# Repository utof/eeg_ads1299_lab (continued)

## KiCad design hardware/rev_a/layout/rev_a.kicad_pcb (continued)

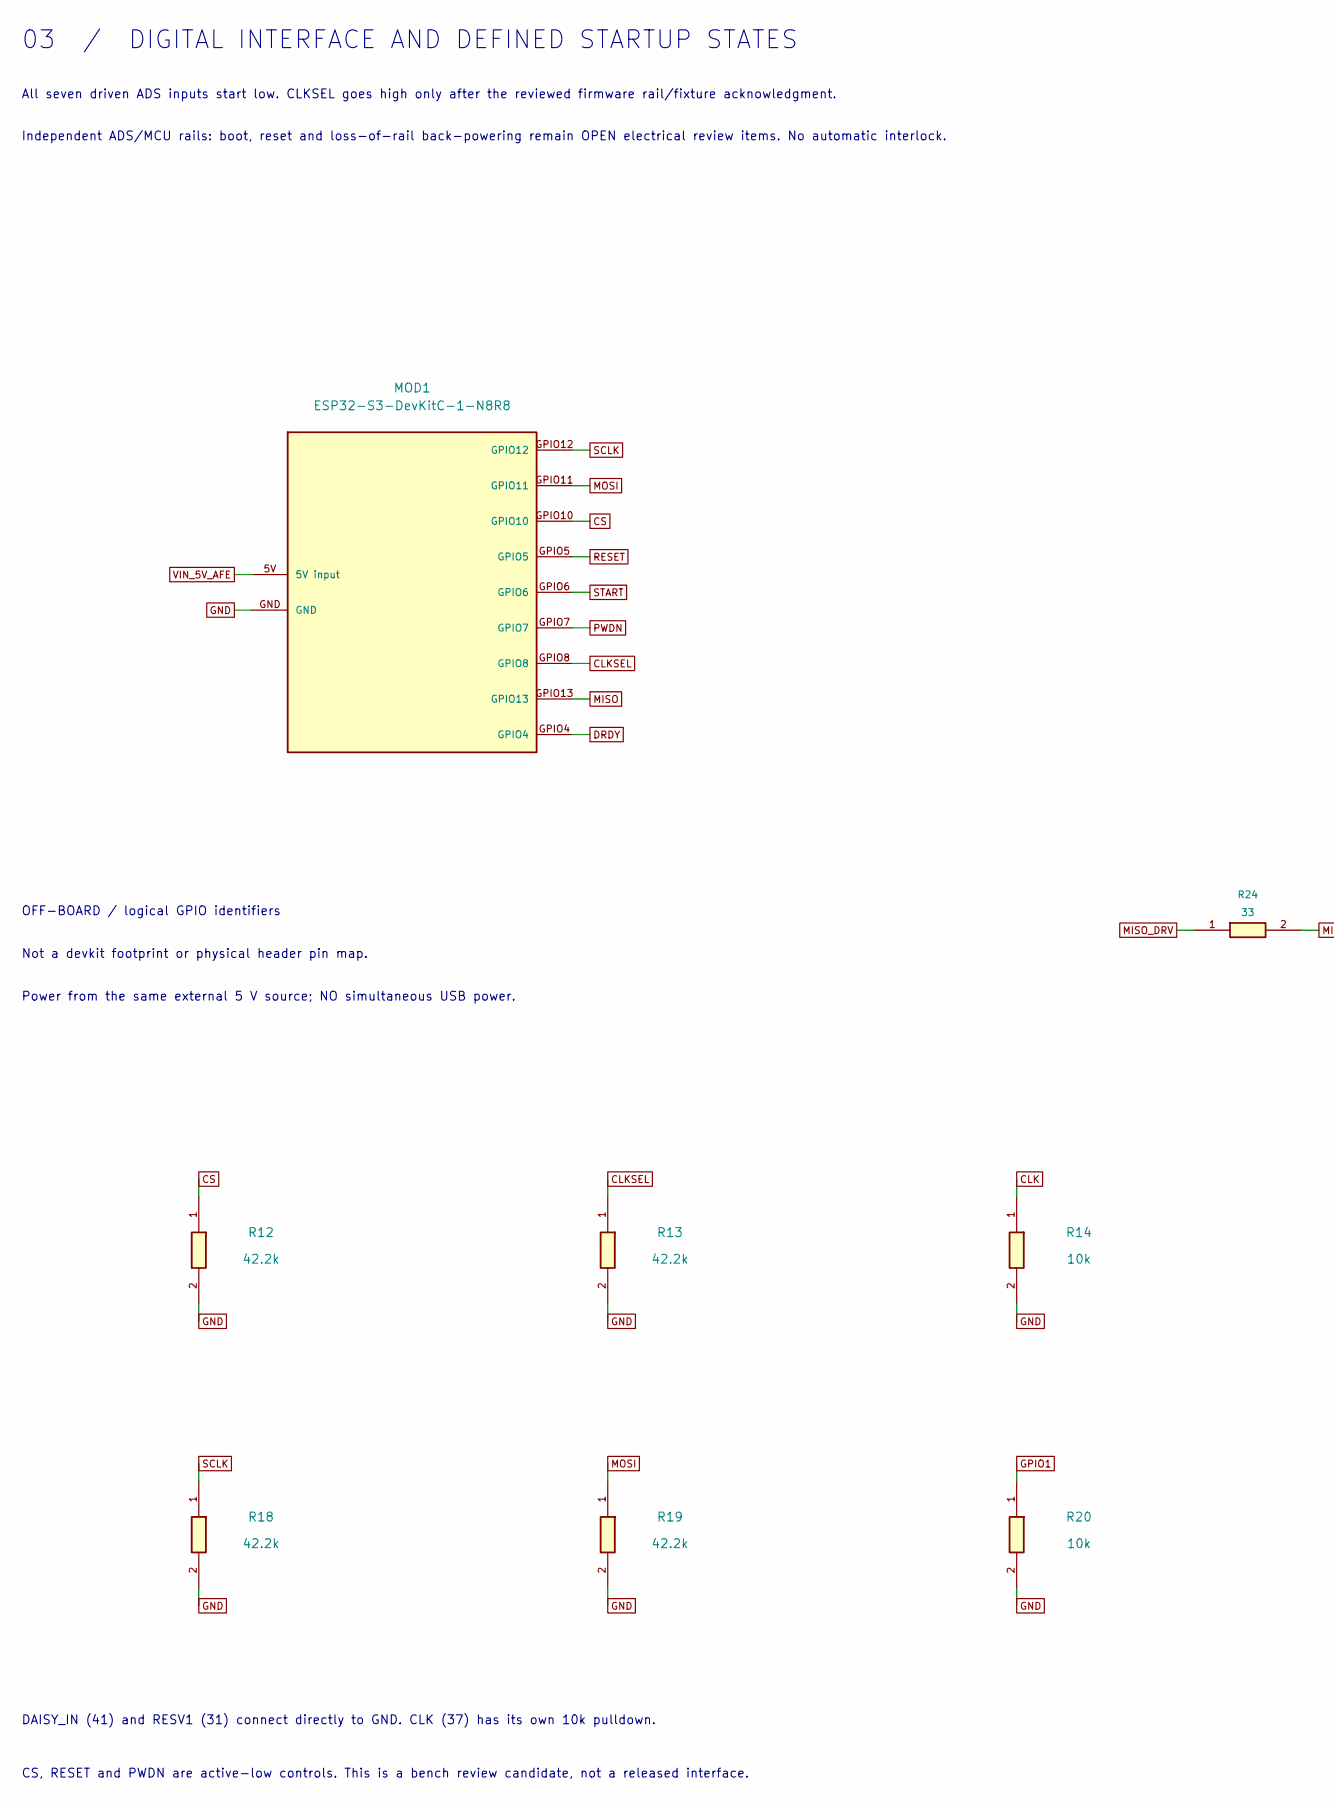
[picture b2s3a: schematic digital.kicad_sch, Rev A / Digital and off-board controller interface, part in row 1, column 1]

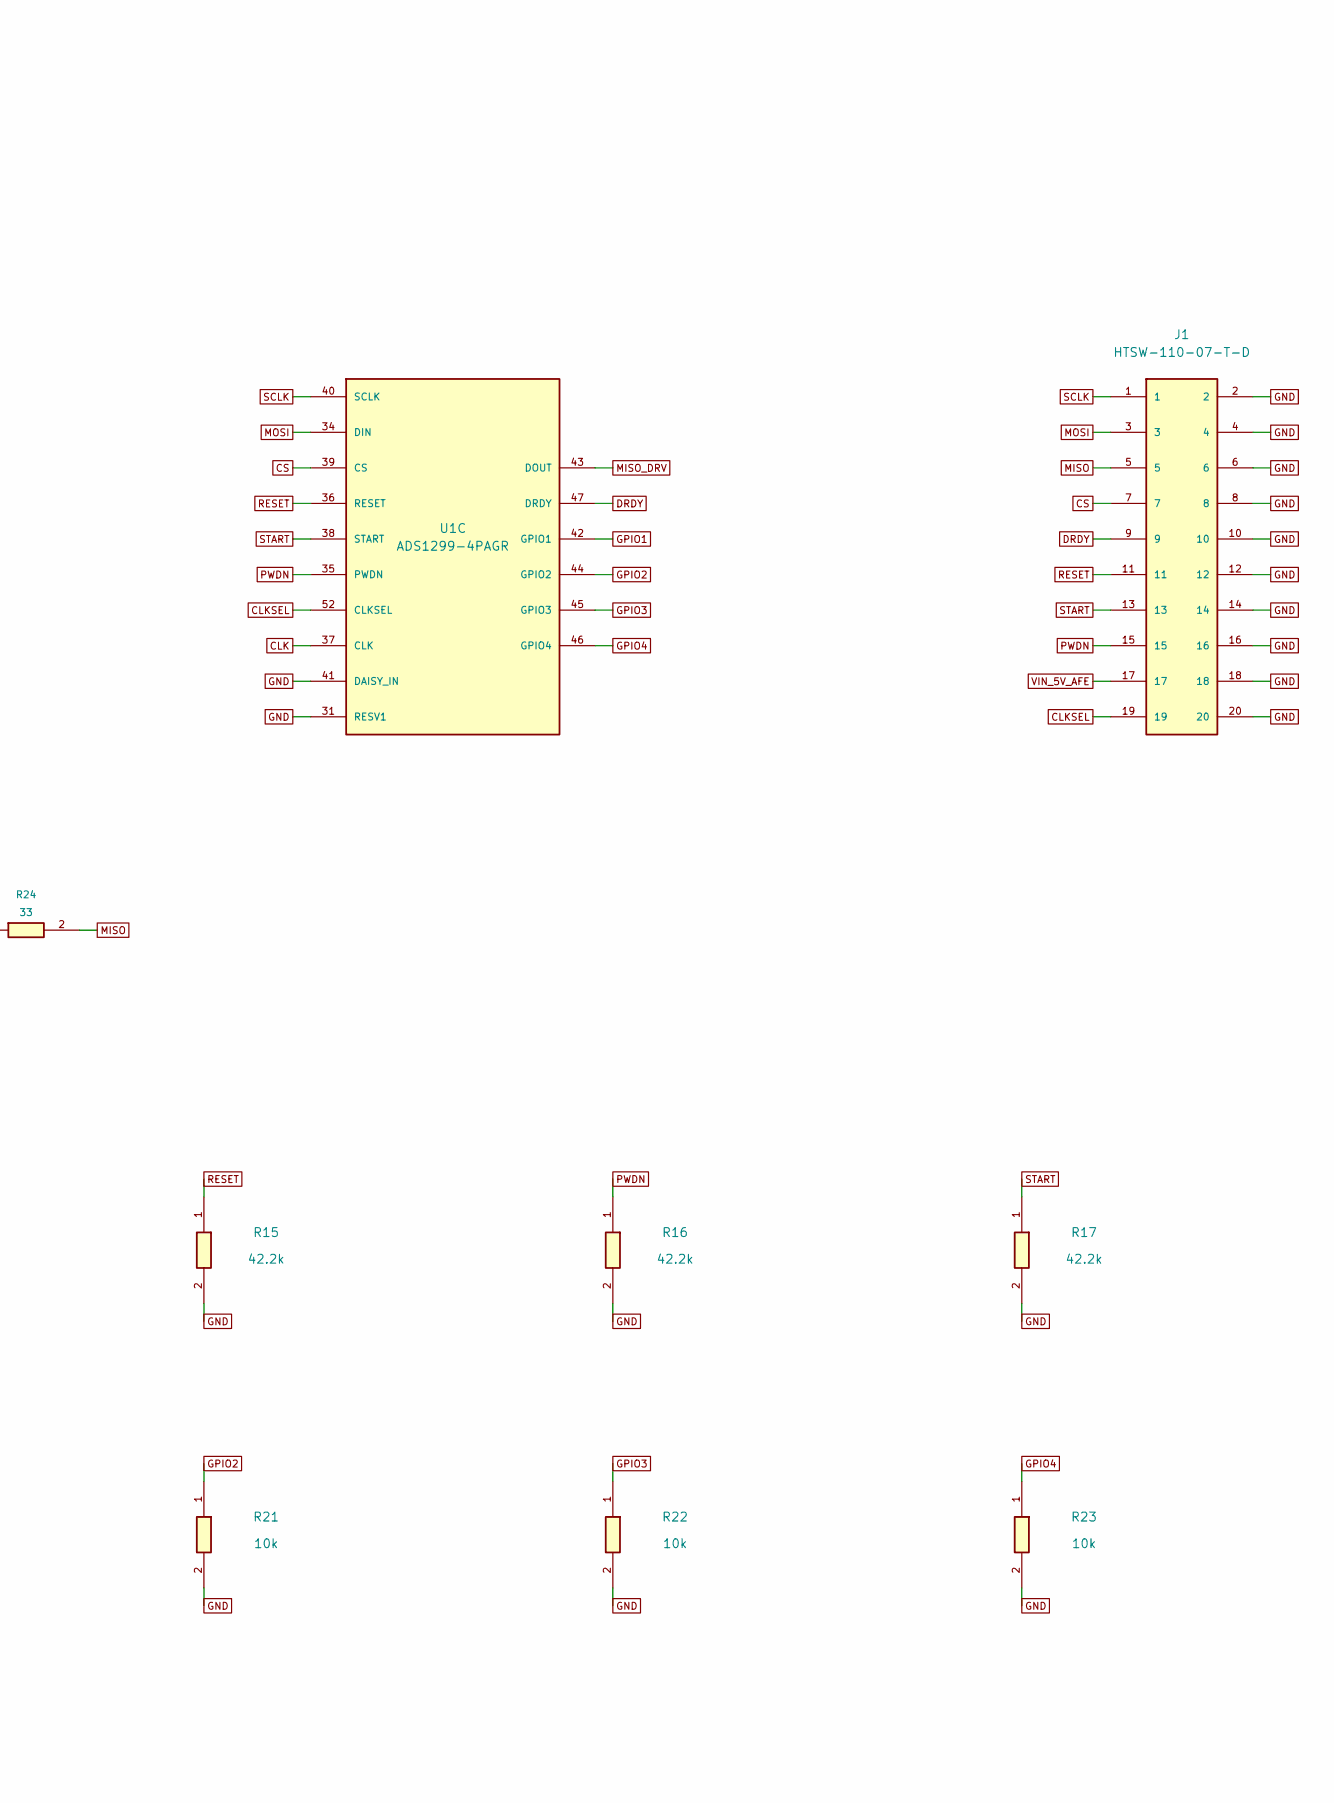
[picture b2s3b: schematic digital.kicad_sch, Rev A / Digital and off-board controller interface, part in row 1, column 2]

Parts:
J1: HTSW-110-07-T-D; PinHeader_2x10_P2.54mm_Vertical; MPN HTSW-110-07-T-D
MOD1: ESP32-S3-DevKitC-1-N8R8; MPN ESP32-S3-DevKitC-1-N8R8
R12, R13, R15, R16, R17, R18, R19: 42.2k; R_0603_1608Metric; Tolerance 0.01; MPN RC0603FR-0742K2L
R14, R20, R21, R22, R23: 10k; R_0603_1608Metric; Tolerance 0.01; MPN RC0603FR-0710KL
R24: 33; R_0603_1608Metric; Tolerance 0.01; MPN RC0603FR-0733RL
U1: ADS1299-4PAGR; TQFP-64_10x10mm_P0.5mm; MPN ADS1299-4PAGR

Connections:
CLK: R14.1, U1.37 (CLK)
CLKSEL: J1.19, MOD1.GPIO8, R13.1, U1.52 (CLKSEL)
CS: J1.7, MOD1.GPIO10, R12.1, U1.39 (CS)
DRDY: J1.9, MOD1.GPIO4, U1.47 (DRDY)
GND: J1.2, J1.4, J1.6, J1.8, J1.10, J1.12, J1.14, J1.16, J1.18, J1.20, MOD1.GND, R12.2, R13.2, R14.2, R15.2, R16.2, R17.2, R18.2, R19.2, R20.2, R21.2, R22.2, R23.2, U1.31 (RESV1), U1.41 (DAISY_IN); also elsewhere on the board
GPIO1: R20.1, U1.42 (GPIO1)
GPIO2: R21.1, U1.44 (GPIO2)
GPIO3: R22.1, U1.45 (GPIO3)
GPIO4: R23.1, U1.46 (GPIO4)
MISO: J1.5, MOD1.GPIO13, R24.2
MISO_DRV: R24.1, U1.43 (DOUT)
MOSI: J1.3, MOD1.GPIO11, R19.1, U1.34 (DIN)
PWDN: J1.15, MOD1.GPIO7, R16.1, U1.35 (PWDN)
RESET: J1.11, MOD1.GPIO5, R15.1, U1.36 (RESET)
SCLK: J1.1, MOD1.GPIO12, R18.1, U1.40 (SCLK)
START: J1.13, MOD1.GPIO6, R17.1, U1.38 (START)
VIN_5V_AFE: J1.17, MOD1.5V (5V input); also elsewhere on the board

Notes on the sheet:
03 / DIGITAL INTERFACE AND DEFINED STARTUP STATES
All seven driven ADS inputs start low. CLKSEL goes high only after the reviewed firmware rail/fixture acknowledgment.
Independent ADS/MCU rails: boot, reset and loss-of-rail back-powering remain OPEN electrical review items. No automatic interlock.
OFF-BOARD / logical GPIO identifiers
Not a devkit footprint or physical header pin map.
Power from the same external 5 V source; NO simultaneous USB power.
DAISY_IN (41) and RESV1 (31) connect directly to GND. CLK (37) has its own 10k pulldown.
CS, RESET and PWDN are active-low controls. This is a bench review candidate, not a released interface.

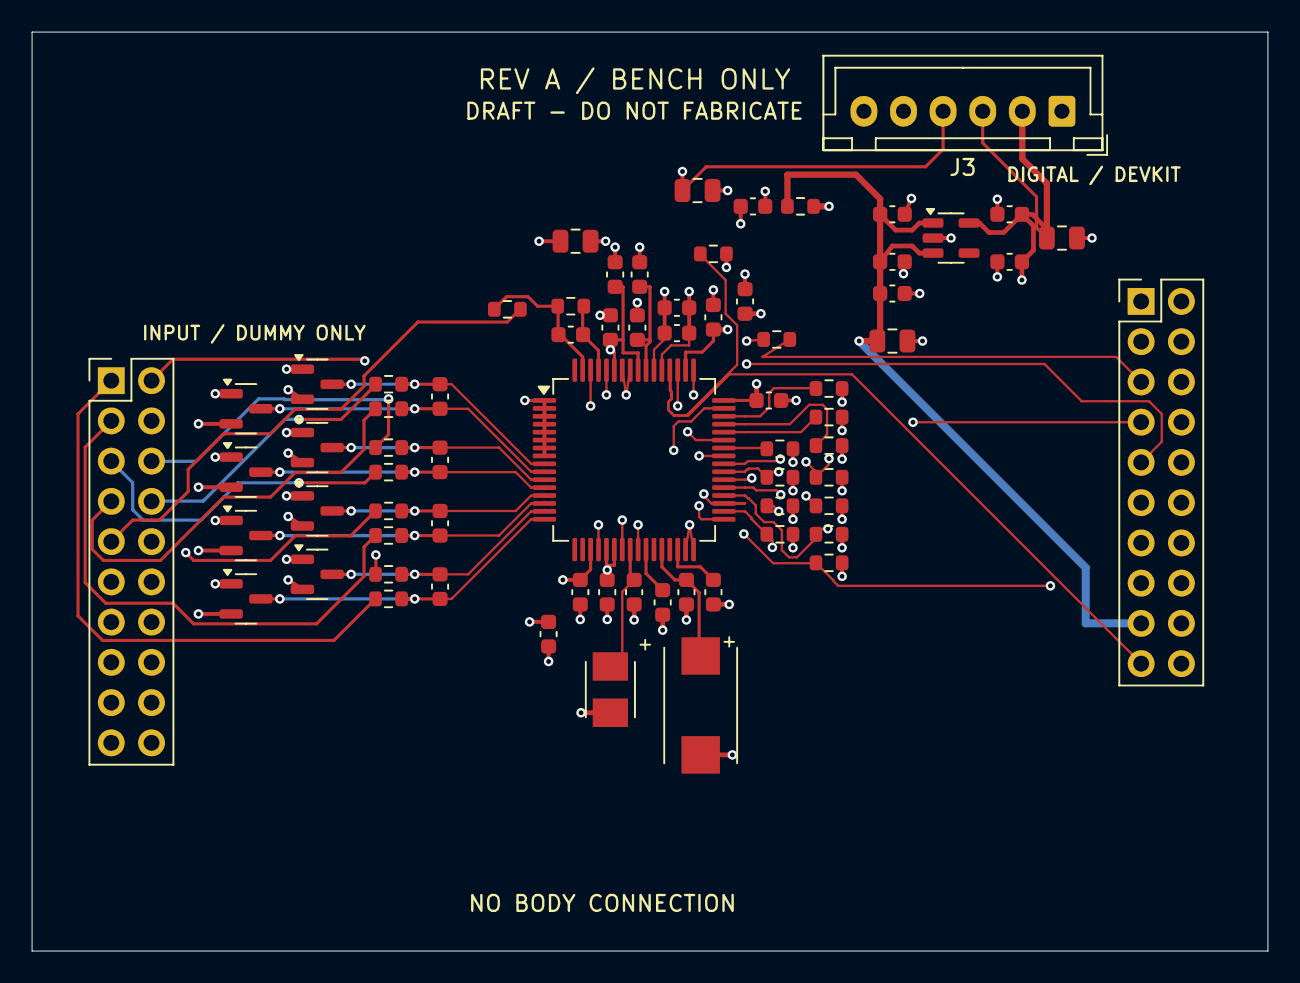
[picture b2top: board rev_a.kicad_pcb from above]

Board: 4 copper layers, 78.0 x 58.0 mm, 70 parts (0 on the bottom side), 43 nets.

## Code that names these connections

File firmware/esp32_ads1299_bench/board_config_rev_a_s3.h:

#pragma once
// Proposed Rev A digital GPIO map only. No wiring, power or human-use approval.
#if !defined(CONFIG_IDF_TARGET_ESP32S3)
#error "EEGLAB_REV_A_S3 requires CONFIG_IDF_TARGET_ESP32S3."
#endif
constexpr int PIN_SCLK = 12;
constexpr int PIN_MISO = 13;
constexpr int PIN_MOSI = 11;
constexpr int PIN_CS = 10;
constexpr int PIN_DRDY = 4;
constexpr int PIN_RESET = 5;
constexpr int PIN_START = 6;
constexpr int PIN_PWDN = 7;
constexpr int PIN_CLKSEL = 8;
constexpr int EXPECTED_ADS_CHANNELS = 4;

#include "bench_console.h"
